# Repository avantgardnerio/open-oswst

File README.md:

# open-oswst

Stealth LoRa radio mesh where the primary design principle is "only speak when spoken to": a simplex push-to-talk voice radio over
LoRa, with flood repeaters, that transmits nothing until someone presses PTT.

## Hardware

- **Board**: [Heltec WiFi LoRa 32 V4.3](https://heltec.org/project/wifi-lora-32-v4/) (ESP32-S3 + SX1262, 863-928 MHz)
- **MCU**: ESP32-S3 rev 0.2, 16MB flash, ~380 KiB RAM, no PSRAM
- **Radio**: Semtech SX1262 LoRa transceiver, 915 MHz ISM band, behind the board's KCT8103L front-end module (PA + LNA), then an
  external "Air Buddy" amplifier. The SX1262 runs at 6 dBm, which should give roughly 1 W out of the Air Buddy (estimated from datasheets,
  not measured)
- **GPS**: L76K on the Heltec's GNSS connector (UTC time and position, logged and shown on screen)
- **Display**: SSD1306 128x64 OLED (I2C)
- **Audio**: MAX9814 electret mic (ADC), MAX98357A I2S class-D speaker amp

The board is a V4.3. All the boards we've tested are; a V4.2 (GC1109 front end) would need different FEM pins and TX power.

### Pin Map

`src/board.rs` is the one place pins are assigned; this table mirrors it.

| Function | GPIO | Notes |
|---|---|---|
| PTT (PRG button) | 0 | Active LOW, internal pull-up |
| VOL encoder A / B / SW | 3 / 6 / 45 | GPIO45 is a strapping pin, safe as a switch to GND |
| Mic (ADC1) | 4 | MAX9814 out |
| Speaker I2S BCLK / DIN / WS | 47 / 33 / 48 | MAX98357A |
| OLED SDA / SCL / RST | 17 / 18 / 21 | |
| Vext power enable | 36 | LOW = on (OLED) |
| LoRa SCK / MOSI / MISO / NSS | 9 / 10 / 11 / 8 | SPI2 |
| LoRa RST / DIO1 / BUSY | 12 / 14 / 13 | |
| FEM power / enable (CSD) | 7 / 2 | Held HIGH while running |
| FEM CTX | 5 | HIGH only during TX (LOW = RX through the LNA) |
| GPS UART RX / TX | 39 / 38 | ESP side. Meshtastic's variant file comments have these the other way round |
| GPS power / reset / wake | 34 / 42 / 40 | Power is active LOW |
| Battery sense | 1 (+ 37 enables the divider) | Free for this on the newest PCB rev; not used by the firmware yet |

## Dev Environment Setup

### Prerequisites

1. **Install Rust + Xtensa toolchain** via [espup](https://github.com/esp-rs/espup):

```bash
cargo install espup
espup install
```

2. **Create an ESP environment export script** (`~/export-esp.sh`):

```bash
export LIBCLANG_PATH="$HOME/.rustup/toolchains/esp/xtensa-esp32-elf-clang/esp-20.1.1_20250829/esp-clang/lib"
export PATH="$HOME/.rustup/toolchains/esp/xtensa-esp-elf/esp-15.2.0_20250920/xtensa-esp-elf/bin:$PATH"
```

The exact paths may vary — check `~/.rustup/toolchains/esp/` after `espup install`.

3. **Install flashing tools**:

```bash
cargo install espflash cargo-espflash ldproxy
```

4. **Python tools** (log pulling, PCB and case generation) live in a venv built with Python 3.13:

```bash
python3.13 -m venv .venv
.venv/bin/pip install -r requirements.txt
```

### Build

```bash
. ~/export-esp.sh
cargo build                      # firmware (repo root, ESP32-S3)
(cd core && cargo test)          # app logic unit tests, on this PC
(cd desktop && cargo run)        # desktop build (a skeleton so far)
```

ESP-IDF v5.5.x is downloaded automatically by `esp-idf-sys` on first build (takes a while).

### Flash

Over USB, use the script. It flashes every connected board at once, and passes the three things a bare `espflash flash` gets wrong:

```bash
. ~/export-esp.sh && cargo build && scripts/flash-all.sh
```

- **our bootloader** (`--bootloader`): it switches the flash to QIO. espflash's bundled one is DIO
- **our partition table** (`--partition-table`): espflash's default drops the `storage` partition and the OTA slots
- **`--erase-parts otadata`**: otherwise a board last updated over WiFi keeps booting the other slot

Over WiFi, see [In the Field](#in-the-field).

Serial ports aren't stable between plug-ins: identify boards by MAC (the ESP32-S3's USB serial number), not by `ttyACM` number. To capture a
boot log from the first line, `python3 scripts/boot-log.py <PORT>`. Never flash while another program holds the port.

### Device Config

Each board's settings are a text file on its storage: `/data/config.toml`. On the newest PCB rev the on-device menu (click the VOL knob)
sets the mode and rewrites the file. Every setting and flag is declared in `core/src/config.rs`; each boot logs their values
and a 4-digit settings profile (also in `/api/status`): radios with different profiles can't hear each other.

```toml
mode = "repeater"        # normal | repeater | echo

[flags]                  # experiments, come and go (core/src/config.rs lists them)

[[wifi]]                 # networks to join, tried in order
ssid = "Starlink"
password = "..."
```

`scripts/provision.py` writes it over USB, from `boards.toml` in the repo root (kept out of git: it holds WiFi passwords; copy
`boards.example.toml` to start). It flashes the firmware too, and **erases the board's storage**, logs included: pull them first.

```bash
.venv/bin/python scripts/provision.py                      # every connected board
.venv/bin/python scripts/provision.py A4:CB:8F:A2:0F:5C    # just this one
```

The boot log shows the result, e.g. `Config: mode=Echo, 1 WiFi network(s)`.

### Logs

Every boot writes a text log to `/data/sd/log/NNNN.txt` on the board's SD card (LittleFS, `src/devices/sd.rs`). Lines are buffered in
RAM and written by a low-priority thread once a second: unlike the chip's own flash, the card stalls nothing, so repeaters log too. No
card, no log. Copy them off over WiFi (WebDAV, below: `/fs/sd/log/`). `scripts/pull-logs.py` reads the flash over USB, so it only
finds logs from before the card.

After an echo test, join the handheld's and the echo station's logs into a per-transmission table and a map (OpenStreetMap/satellite,
one circle per transmission coloured by how well each direction got through, plus GeoJSON for QGIS):

```bash
.venv/bin/python scripts/range-report.py <handheld log> <echo station log>
```

## In the Field

Every radio has the field hotspot (Starlink) in its `config.toml` and stays on WiFi, so in the field the laptop does everything over
WiFi: find the radios, read their status and logs, change their config, update their firmware. USB is the fallback.

### Laptop setup (once, at home)

```bash
sudo apt install avahi-utils curl    # avahi-browse finds the radios; Ubuntu resolves *.local out of the box
```

Plus the build tools above (`espup`, `espflash`, `~/export-esp.sh`), so firmware can be built and saved as an image in the field.

### Find the radios

Join the laptop to the same network as the radios, then:

```bash
avahi-browse -rtp _oswst._tcp | grep "^="    # one line per radio: name, host, IP, port
```

Each radio is `oswst-XXXX.local`, from the last 4 hex digits of its MAC (A4:CB:8F:A2:0F:5C is `oswst-0f5c`). A radio joins WiFi ~7 s
after boot. If a radio doesn't show up:

- `getent hosts oswst-0f5c.local`: asks for one radio by name
- check that avahi-browse ran at all. Don't pipe its errors into grep: if it isn't installed, `2>&1 | grep` prints nothing,
  which looks exactly like "no radios"
- last resort, scan the subnet for the API:
  `for i in $(seq 1 254); do curl -s -m 1 http://192.168.0.$i/api/status | grep -q mac && echo 192.168.0.$i & done; wait`

### Talk to a radio

In a browser: `http://oswst-XXXX.local/` (or its IP) opens the radio's web page, its status and a live picture of its screen
(`www/`, served by the radio itself: no internet needed).

Port 80, no password (the WiFi password is the security). `/fs/` is the radio's storage as a read-write WebDAV folder
(`src/webdav.rs`): open `dav://oswst-XXXX.local/fs/` in a file manager, or:

```bash
R=oswst-0f5c.local
curl http://$R/api/status                     # name, MAC, firmware (git hash, confirmed?), OTA slot, mode, uptime, heap
gio list -l dav://$R/fs/sd/log/               # after `gio mount dav://$R/fs/`
curl -O http://$R/fs/sd/log/0007.txt          # fetch a log: 25 KB in under 0.1 s (vs ~80 s over USB)
curl -O http://$R/fs/config.toml              # the settings
curl -T config.toml http://$R/fs/config.toml  # replace them (checked first: a bad file is refused); apply on reboot
curl -X POST http://$R/api/reboot
curl -X POST http://$R/api/wifi/off           # WiFi off until the next power cycle (for timing-sensitive tests)
```

`/api/wifi/off` isn't saved: every boot starts with WiFi on again, so a power cycle always gets the radio back on the network. Once it's
off, the radio can't be reached over WiFi until then.

### Update firmware over WiFi (OTA)

Build, save an app image, put it on the radio as `/fs/sd/firmware.bin` (an ordinary file: a file manager works too), then
`POST /api/ota`: the radio copies it into its spare slot and reboots into it (back up in ~15 s). `/api/status` then shows the new
git hash, the other slot and `"firmware_state":"pending"`: a new app must run a minute (then `valid`), or the radio goes back to the
old one. `GET /api/firmware` downloads the app a radio is running.

```bash
. ~/export-esp.sh && cargo build
espflash save-image --chip esp32s3 target/xtensa-esp32s3-espidf/debug/open-oswst app.bin
curl -T app.bin http://oswst-0f5c.local/fs/sd/firmware.bin && curl -X POST http://oswst-0f5c.local/api/ota
```

Every radio found:

```bash
for host in $(avahi-browse -rtp _oswst._tcp | grep "^=" | cut -d';' -f7 | sort -u); do
    curl -T app.bin http://$host/fs/sd/firmware.bin && curl -X POST http://$host/api/ota
done
```

### USB fallback

When a radio isn't on WiFi:

- **Flash:** `scripts/flash-all.sh`. It passes our bootloader, our partition table and `--erase-parts otadata`, which a bare
  `espflash flash` gets wrong.
- **Pull logs:** `scripts/pull-logs.py` (~80 s).
- **Watch a boot:** `scripts/boot-log.py`.

Identify boards by MAC, not by `ttyACM` number, and never flash while another program holds the port.

## Management Server

Radios get updates from a management server (`server/`, issue #34) that they dial out to: nothing on a radio listens for it. Every
connection is Noise: a radio must know the server's public key, and the server must find the radio's in its list, or it's refused.
The server's files live in one folder outside the repo (default `/srv/oswst`):

```
server.key      the server's key pair (mode 0600)
radios.toml     the radios allowed in: re-read at every connection, no restart needed
bundle.tar.gz   THE update: radios that don't have it are offered it
```

```bash
cd server && cargo run --release -- keygen /srv/oswst     # once: prints the server's public key
cd server && cargo run --release -- /srv/oswst            # run it by hand (port 3101)
```

To keep it running, install it as the systemd service `oswst-server` (`server/oswst-server.service`). It runs as its own user,
`oswst`, which can only read `/srv/oswst`. Run the same script again after you change `server/`:

```bash
scripts/install-server.sh                                 # build, install, (re)start
sudo journalctl -u oswst-server -f                        # its log
```

### Publish an update

```bash
scripts/publish-firmware.sh          # builds, then writes /srv/oswst/bundle.tar.gz
```

A bundle (`core/src/bundle.rs`) is one `.tar.gz`: `firmware.bin` for the radio's spare app slot, and `www/` (the web page, with
only the `node_modules` files its import map names) for its storage. The server notices the new file by itself.

### Install it

On the radio: **menu, Update**. It shows the version and size, then **Install** runs three steps, each in percent: **Downloading**
(to the storage), **Verifying** (its SHA-256), **Extracting** (the firmware into the spare slot, marked to boot only once every
file is written; the files onto the storage, never touching `config.toml` or `secrets.toml`). Then it reboots into the new
firmware, which must run a minute to be kept. A radio that has the bundle is told **Up to date**.

`POST /api/management/update` does the same from a laptop. Radios on firmware from before bundles are offered just the firmware
inside the bundle; one more Update then gets the whole bundle.

### Set up a new radio

1. **Provision over USB** (once). Give the radio an entry in `boards.toml` (its mode, name, WiFi networks), then:

   ```bash
   . ~/export-esp.sh && cargo build
   .venv/bin/python scripts/provision.py 10:BD:A3:5A:EB:7C
   ```

   This flashes the firmware and writes a fresh storage holding just its `config.toml` (it **erases** the storage). The radio
   boots, joins WiFi, and makes its own key pair: the private key never leaves it.
2. **Enroll it on the server.** Its public key is on its status page; add it to `/srv/oswst/radios.toml`:

   ```bash
   curl -s http://oswst-eb7c.local/api/status    # "management": {"radio_public_key": "..."}
   ```

   ```toml
   [[radio]]
   name = "Repeater"
   mac = "10:BD:A3:5A:EB:7C"
   public_key = "38389dbc..."
   ```
3. **Tell it where the server is** (and the server's public key, from `keygen`):

   ```bash
   curl -X PUT -H "Content-Type: application/json" \
        -d '{"host": "<server host>", "port": 3101, "server_public_key": "<64 hex digits>"}' \
        http://oswst-eb7c.local/api/management
   ```
4. **Menu, Update.** A radio flashed over USB doesn't have the bundle yet, so it's offered it: that brings the web page too.

A re-provisioned radio has a new key (the storage was erased), so it's enrolled again: replace its `public_key` in `radios.toml`.
To shut a lost radio out, delete its entry.

## Current Behavior

- **Voice**: simplex push-to-talk. Hold PTT to talk: audio is Codec2-encoded at 1200 bps and streamed as 4-frame LoRa packets (160 ms of
  audio each, SF7/125 kHz). Release to listen: received packets are decoded in order and played through the speaker. A lost packet
  costs one 160 ms gap of silence, and a corrupt one is dropped rather than resetting playback. PTT does nothing while someone else's
  transmission is on the air: no talking over each other
- **Modes**: normal; **repeater** (relays the first copy of each packet once, one hop further: flood style, but a copy that loops back
  is a duplicate); **echo** (records a transmission, then plays it back over the air, for range testing alone). Set in
  `/data/config.toml`
- **Screen**: short MAC and UTC time, GPS position, RX/TX state, RSSI and SNR of received audio, and volume
- **Controls**: VOL knob turns volume; clicking it opens the menu (Lock, Mode). Needs the newest PCB rev's wiring (see Pin Map)
- **Logs**: persistent per-boot text logs including a GPS fix every 30 s, so field tests can be mapped afterwards
- **Timing**: the air is a conveyor of 80 ms bins (`core/src/conveyor.rs`). A talker sends packet n in bin 2n and each repeater relays
  it one bin later, so hop h of packet n is in bin 2n + h; the header's hop count says which. Every packet starts at its microsecond, in
  the middle of its bin (the radio sends it then). A receiver counts bins from the first good packet it hears, so every copy of a packet
  is the same packet, and a garbled packet in a bin still keeps the transmission going. Only a talker's first packet waits for clear air
- **Listening**: during a transmission the radio turns through a schedule of channels, bin by bin (`core/src/climb.rs`): it holds the
  channel with the strongest copies in their bins, and in the others always seeks one channel on and one back. A side that's clearly
  stronger becomes the hold, so a listener climbs to the best copy of several repeaters'. Only the first copy of each packet plays
- **Next up**: frequency hopping and encryption

<!-- air-diagram: generated by scripts/air-diagram.py; edit the script, not this section -->
## On the Air (SF7 / 125 kHz)

LoRa SF7, 125 kHz, coding rate 4/5, explicit header, 12-symbol preamble (`core/src/air.rs`). One symbol is 2^7 / 125 kHz =
**1.024 ms**. Air times are Semtech's formula on our constants; regenerate this section with `python3 scripts/air-diagram.py`
after changing one.

### Voice packet: 26 bytes, 64.25 symbols, 65.8 ms

```
symbol 0           12     16.25   24.25                                   64.25
       +-----------+------+-------+----+----+----+----+----+----+----+----+
       |  preamble | sync |  PHY  | B1 | B2 | B3 | B4 | B5 | B6 | B7 | B8 |
       |   12 sym  | 4.25 | header|            8 blocks x 5 sym           |
       |           | sym  | 8 sym |        28 bits each = 224 bits        |
       |           |      |       |        = 26 B payload + 2 B CRC       |
       +-----------+------+-------+----+----+----+----+----+----+----+----+
ms     0           12.3   16.6    24.8                                    65.8
```

- **sync**: 2 sync-word symbols + 2.25 start-of-frame symbols
- **CRC**: ours (`core/src/crc.rs`, CRC-16/CCITT-FALSE), appended and checked by the radio driver, with LoRa's own CRC off: the
  same 16 bits on the air. LoRa only checks its CRC if the received header says there is one, and noise can corrupt a header
  into "no CRC" and still pass its checksum; ours is checked on every packet, so garbage never reaches the app
- **PHY header**: 20 bits (payload length, coding rate, CRC flag (off), header checksum), always sent at CR 4/8: 8 symbols (at
  SF7, nothing else fits)
- **blocks**: each 5-symbol block carries 28 data bits. 26 bytes + CRC fill 8 blocks exactly; one more byte costs another block
  (+5 symbols, +5.1 ms)

The 26 bytes:

```
byte   0               2           8           14          20          26
       +---------------+-----------+-----------+-----------+-----------+
       |   our header  |   Codec2  |   Codec2  |   Codec2  |   Codec2  |
       |   (2 bytes)   |  frame 1  |  frame 2  |  frame 3  |  frame 4  |
       |               |  6 bytes  |  6 bytes  |  6 bytes  |  6 bytes  |
       |               |  = 40 ms  |  = 40 ms  |  = 40 ms  |  = 40 ms  |
       +---------------+-----------+-----------+-----------+-----------+

our header, 16 bits, big-endian (core/src/packet.rs):
bit     15     11 10          4 3       1 0        0
       +---------+-------------+---------+----------+
       | type 5b |   txid 7b   | hops 3b | spare 1b |
       +---------+-------------+---------+----------+
       type: 0 voice, 1 echo replay, 2 wake, 3 voice end, 4 echo end (core/src/packet.rs PacketType)
       txid: random per transmission; hops: repeaters this copy came through, 0 from the talker; spare: 0
```

### Wake packet: 2 bytes, 64.25 symbols, 65.8 ms

Sent once, first, so radios sweeping the hop channels can find the transmission. The preamble takes up the air the audio would
have used, so it fits a slot like any packet: 12 + (48 − 18) = 42 symbols.

```
symbol 0                                         42     46.25   54.25     64.25
       +-----------------------------------------+------+-------+----+----+
       |                 preamble                | sync |  PHY  | B1 | B2 |
       |      42 sym: a sweeping radio's CAD     | 4.25 | header| 2 B hdr |
       |      (2 sym) can land in the first      | sym  | 8 sym |  + CRC  |
       |            40 symbols (41 ms)           |      |       |         |
       +-----------------------------------------+------+-------+----+----+
ms     0                                         43.0   47.4    55.6      65.8
```

### End packet (EOT): 26 bytes, 64.25 symbols, 65.8 ms

The last packet of every transmission says who sent it and where they were: a voice packet's size and air, so it fits a
repeater's slot like one. The talker sends its own; a repeater relays it unchanged; an echo station ends its replay with its
own. The screen shows who was last heard, how far away, and through a repeater or not.

```
byte   0               2           5           8                                26
       +---------------+-----------+-----------+--------------------------------+
       |  our header   | latitude  | longitude |  name, UTF-8, up to 18 bytes   |
       | type 3 or 4   | 24 bits   | 24 bits   |          zero-padded           |
       +---------------+-----------+-----------+--------------------------------+
       latitude: ±90° in ±2^23 steps (~1.2 m); longitude: ±180° (~2.4 m); -2^23 latitude = no fix
```

### A transmission

```
PTT pressed
 +160 ms   wake packet         64.25 sym   (sent while the first 160 ms of audio is captured)
 ~320 ms   voice packet 0      64.25 sym   then one voice packet every 160 ms (156.25 sym)
     ...
 release   last voice packet, then EOT    64.25 sym  (who and where)
```

An echo station sends its wake packet one slot before its replay. A repeater relays a wake packet like any other (once per
transmission), so radios that only hear the repeater can find it.

### One slot with a repeater: 160 ms = 156.25 symbols

Talkers don't hop yet (`tx_hops = 0`): every transmission stays on the start slot, channel 0. Receivers sweep `rx_hops`
channels, and with the sweep flag a repeater relays each packet on the next of those after the one it heard it on (channel 1
here), then goes back to listening on channel 0. It relays as soon as it has the packet, inside the gap before the talker's next
one. Repeater steps are medians of 226 relays (the talker's packets and the echo station's replays) measured on the desk
(`out/relay-test/20261005-150052`).

```
symbol    0                               64.25                                137      156.25
          |                               |                                    |        |
talker    [=== voice packet n ============]                                             [== packet n+1
repeater   . RX (locked) .................]ttt[===== relay of packet n ========]b. RX ..[
                                           ^ t: RX done -> relay on air 7.8 ms
                                                                                ^ b: back to RX 1.5 ms
                                                                                <-- slack 17.9 ms -->
ms        0                               65.8                                 140.6    160
```

| Step (repeater) | Median | Symbols | |
|---|---|---|---|
| RX done → relay starts | 5.4 ms | 5.2 | `t`: read the packet out, the app hands it back to the radio |
| standby | 0.9 ms | 0.8 | `t` |
| prep (packet, modulation, buffer) | 1.5 ms | 1.5 | `t` |
| tx: TX command → TxDone | 67.1 ms | 65.5 | 65.8 ms on the air + PA ramp and IRQ |
| back to RX | 1.5 ms | 1.5 | `b` |
| **slack before packet n+1** | **17.9 ms** | **17.5** | a relay ending later than this deafens the repeater to the next packet |

Each repeater uses ~142 of the 160 ms. A second repeater in the chain can't fit the same slot on the same channel; that's what
hopping (each repeater relays on the next channel) is for.
<!-- /air-diagram -->

## Key Implementation Notes

- **Framework**: esp-idf-svc 0.52.1 (std Rust, not bare-metal)
- **Async**: `block_on` + `embassy_futures::select`; the app sleeps until an event (packet, PTT, speaker, knob) or a 250 ms housekeeping tick
- **LoRa driver**: `lora-phy` (lora-rs git main) with `GenericSx126xInterfaceVariant`; DIO2 drives the FEM's TX/RX path, GPIO5 its RX LNA
- **Hardware-free app**: everything above the drivers is in `core/` behind small device traits, so it runs and is tested on a PC
- **Storage**: LittleFS (`joltwallet/littlefs` component), chosen over FAT for power-cut safety: the flash partition at `/data` holds
  the settings (`config.toml`, `secrets.toml`); the SD card at `/data/sd` everything else (logs, web app, updates)
- **SPI async**: `CONFIG_SPI_MASTER_ISR_IN_IRAM` disabled in `sdkconfig.defaults`
- **defmt workaround**: `defmt-discard.x` linker script discards defmt sections that break ESP-IDF flash layout
- **Stack**: 65536 bytes for main task (Codec2 init needs large stack temporaries)

## Project Structure

Four Cargo workspaces. Each opens as its own IDE project: the firmware builds for the ESP32-S3, the others for this PC.

```
src/                 # Firmware (repo root workspace, xtensa)
  main.rs            #   Brings up the board and runs the core app on it
  board.rs           #   The one place pins are assigned
  devices/           #   ESP drivers: radio, fem, gps, mic, speaker, screen, encoder, ptt, settings, storage
  bin/               #   Bringup tests (fem_probe, gps_test, storage_test, batt_probe, loopbacks, ...)
core/                # Hardware-free app: its own workspace, so `cargo test` runs on this PC
  src/app.rs         #   Event loop, screens, housekeeping
  src/conveyor.rs    #   A transmission's bins: which packet each copy is, when it's over (unit tested)
  src/climb.rs       #   Which channel to listen on, bin by bin: hold the strongest copy, seek beside it (unit tested)
  src/playout.rs     #   Decoded packets to the speaker in order, silence for lost ones (unit tested)
  src/codec.rs       #   Codec2 thread
  src/management.rs  #   The management server's protocol (Noise), shared with server/
  src/bundle.rs, tar.rs, gzip.rs   # Update bundles: what goes where, streamed off a .tar.gz (unit tested)
  src/echo.rs, mode.rs, menu.rs, packet.rs, logger.rs
  src/devices/       #   Device interfaces: radio/speaker/screen channels, gps/mic/ptt/knob/settings traits
desktop/             # Desktop build on virtual devices (skeleton so far)
server/              # The management server: radios' keys, update bundles
www/                 # The radio's web page (preact + htm, no build step), shipped in bundles
scripts/             # provision.py, publish-firmware.sh, boot-log.py, pull-logs.py, ...
pcb/                 # PCB definition (Python DSL) and generated KiCad board
models/              # Parametric case (build123d) and fit check
partitions.csv       # Partition table: two OTA app slots, LittleFS storage (/data)
boards.example.toml  # Per-board settings for scripts/provision.py (copy to boards.toml)
sdkconfig.defaults   # ESP-IDF config overrides
```

## Bill of Materials

### Handset (~$122)

| Component                                                                                       | Part                                                       | Qty | Est. Cost |
|-------------------------------------------------------------------------------------------------|------------------------------------------------------------|-----|-----------|
| [MCU + LoRa + GPS](https://www.amazon.com/dp/B0GCD9W6JZ?ref=ppx_yo2ov_dt_b_fed_asin_title&th=1) | Heltec WiFi LoRa 32 V4                                     | 1   | $42       |
| [RF amplifier](https://www.amazon.com/dp/B0DQBJVR91?ref=ppx_yo2ov_dt_b_fed_asin_title)          | AB-IOT-868 "Air Buddy" (902-928 MHz, bidirectional TX+LNA) | 1   | $26       |
| [Speaker amp](https://www.amazon.com/dp/B0DPJRLMDJ?ref=ppx_yo2ov_dt_b_fed_asin_title)           | MAX98357A I2S Class D breakout                             | 1   | $3        |
| [Speaker](https://www.amazon.com/dp/B0BTP67F81?ref=ppx_yo2ov_dt_b_fed_asin_title&th=1)          | 8 ohm 1W mini (JST-PH1.25mm)                               | 1   | $2.50     |
| [Microphone](https://www.amazon.com/dp/B0B7SP6GYX?ref=ppx_yo2ov_dt_b_fed_asin_title)            | MAX9814 electret with AGC (analog out)                     | 1   | $4        |
| [Antenna](https://www.amazon.com/dp/B0D47HVCK7?ref=ppx_yo2ov_dt_b_fed_asin_title&th=1)          | 5 dBi SMA whip (915 MHz)                                   | 1   | $6        |
| [Battery](https://www.amazon.com/dp/B0FPCWFFYB?ref=ppx_yo2ov_dt_b_fed_asin_title)               | YELUFT 1S 103450 3.7V 2000mAh LiPo (JST 1.25)              | 1   | $24       |
| [encoder](https://www.amazon.com/dp/B07F24TRYG?ref=ppx_yo2ov_dt_b_fed_asin_title)               | EC11 rotary encoder w/ push button (Taiss)                 | 2   | $1.25     |
| [Power switch](https://www.amazon.com/dp/B0DN69L9SG?ref=ppx_yo2ov_dt_b_fed_asin_title&th=1)     | SS12F15 mini slide switch (SPDT)                           | 1   | $0.30     |
| [PTT button](https://www.amazon.com/dp/B015X34IP6?ref=ppx_yo2ov_dt_b_fed_asin_title&th=1)       | Ulincos U16A1 16mm metal momentary, flush                  | 1   | $8        |
| [Speaker jack](https://www.amazon.com/dp/B01ASF0LW8?ref=ppx_yo2ov_dt_b_fed_asin_title)          | 2.5mm TRS chassis mount (Calrad 30-714 or similar)         | 1   | $0.66     |
| [Mic/PTT jack](https://www.amazon.com/dp/B00ZYWJ1DG?ref=ppx_yo2ov_dt_b_fed_asin_title)          | 3.5mm TRS chassis mount w/ switch (CESS)                   | 1   | $2        |
| [F2F SMA](https://www.amazon.com/dp/B0FB3R5WRL?ref=ppx_yo2ov_dt_b_fed_asin_title&th=1)          | Female to Female SMA                                       | 1 | $1        |

## Related Projects

Voice over LoRa is rare. This is what we found as of October 2026, with our own status stated the same way as everyone else's.

| Project | What it does | Repeating | Licence | Status |
|---|---|---|---|---|
| **open-oswst** (this) | Live push-to-talk, Codec2 1200 bps, handheld with case and PCB | Flood repeater mode exists, but more than one repeater degrades audio; making multi-repeater flooding work is the current focus | None (US 902–928 MHz ISM) | Live voice works handheld to handheld; field-tested to ~600 m through suburbs (GPS-logged). No encryption or frequency hopping yet |
| [QMesh](https://github.com/faydr/QMesh) ([project](https://hackaday.io/project/161491-qmesh-a-lora-based-voice-mesh-network), [paper](https://cdn.hackaday.io/files/1614916909230944/TAPR%20DCC%202020%20Paper.pdf)) | Live voice, Codec2, 160 ms frames | **Synchronised flooding:** every node retransmits at once in TDMA slots, with extra FEC and deliberate timing/frequency offsets so the copies don't destructively collide, plus per-packet hopping. Reported 99% packet reception with 2–3 simultaneous retransmitters | Amateur (US Technician) | **Ahead of us on radio techniques.** STM32 dev boards + custom shield. No commits since December 2022 |
| [Mesh-Talkie](https://github.com/WIH4/Mesh-Talkie) | Planned PTT handheld, ESP32-S3 + SX1262 (our hardware), AES-256 | Planned flood mesh with TTL | None (EU SRD) | Design documents only: no hardware or firmware yet |
| [esp32_loradv](https://github.com/sh123/esp32_loradv) | Codec2/Opus digital-voice walkie-talkie | None (point to point) | Amateur (70 cm) | Hobby project |
| Meshtastic, [MeshCore](https://github.com/RipeStore/meshcorebuilder), [MeshTRX](https://github.com/StanislavButkovsky/meshtrx) | Text mesh messengers | Yes, for text | None | Mature for text; voice is recorded clips forwarded later, not live PTT |
| [dudmuck/lora_codec2](https://github.com/dudmuck/lora_codec2), [Lora-Voice-Image-Text](https://github.com/chicodog530/Lora-Voice-Image-Text), [ESP32_Codec2](https://github.com/deulis/ESP32_Codec2) | Codec2-over-LoRa demos | None | — | Demos |

As far as we can tell, nobody else has live push-to-talk voice over LoRa working on handhelds **without a licence**. The hard part, several repeaters sharing one channel, is unsolved here; QMesh has gone furthest on it, and under an amateur licence.

## License

TBD

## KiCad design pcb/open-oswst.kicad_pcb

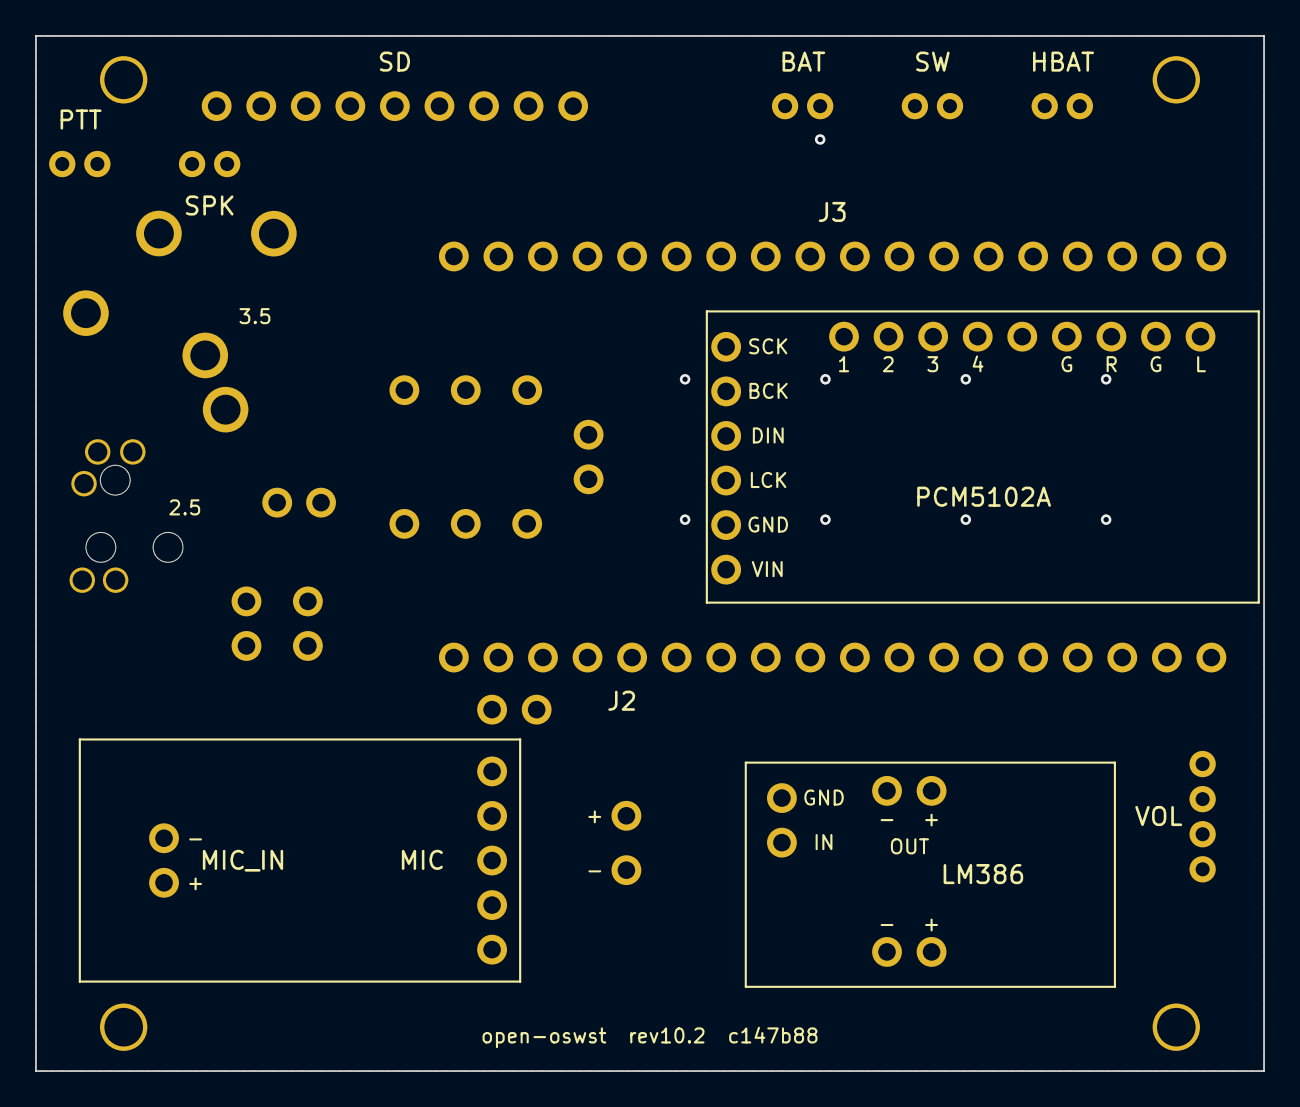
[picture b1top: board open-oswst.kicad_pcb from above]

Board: 2 copper layers, 70.0 x 59.0 mm, 28 parts (0 on the bottom side), 22 nets, no tracks yet.

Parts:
BAT: JST_PH_B2B
C1: PinHeader_1x2_P2.5mm
C2, C3, C4: PinHeader_1x2_P2.54mm
CAPSULE: PinHeader_1x2_P3.1mm
H1, H2, H3, H4: MountingHole_2.2mm
HBAT: JST_PH_B2B
J2, J3: PinHeader_1x18_P2.54mm
JP1: PinHeader_1x2_P2.54mm
K1_2.5: K1_Jack_2.5mm_measured
K1_3.5: K1_Jack_3.5mm_measured
LM386: LM386_mini
MIC: PinHeader_1x5_P2.54mm
MIC_IN: PinHeader_1x2_P2.54mm
PCM: PCM5102A_GY
PTT: JST_PH_B2B
R1, R2, R3: PinHeader_1x2_P7.62mm
SD: PinHeader_1x9_P2.54mm
SPK: JST_PH_B2B
SW: JST_PH_B2B
VOL: JST_PH_B4B

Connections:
ADC: C2.1, J3.GPIO4, R3.2
AMP_IN: LM386.2, PCM.7
AMP_OUT: K1_2.5.2, LM386.4
BCLK: J2.GPIO47, PCM.5
BIAS: C1.+, R1.2, R2.1
CAPSULE: CAPSULE.+, K1_3.5.4
DIN: J2.GPIO33, PCM.4
GND: BAT.-, HBAT.-, J2.GND, J3.GND, JP1.GND, LM386.1, LM386.3, LM386.5, PCM.2, PCM.6, PCM.12, PCM.14, PCM.15, PTT.2, SD.GND, SPK.-, VOL.GND
KNOB_SCL: J3.GPIO6, VOL.SCL
KNOB_SDA: J3.GPIO3, VOL.SDA
LRC: J2.GPIO48, PCM.3
MIC_GND: C1.-, C2.2, C3.2, C4.2, CAPSULE.-, JP1.MIC_GND, K1_2.5.3, MIC.GND, MIC_IN.-
MIC_IN: C3.1, C4.1, K1_3.5.5, MIC_IN.+, R2.2
MIC_OUT: MIC.OUT, R3.1
PTT: J2.GPIO0, K1_3.5.3, PTT.1
SD_CLK: J3.GPIO45, SD.CLK
SD_CMD: J2.GPIO43, SD.CMD
SD_D0: J2.GPIO44, SD.DO
SPK+: K1_2.5.1, SPK.+
VBAT: BAT.+, SW.1
VSW: HBAT.+, SW.2
Ve: J2.Ve_a, J2.Ve_b, LM386.6, MIC.GAIN, MIC.VDD, PCM.1, PCM.13, R1.1, SD.3V3, SD.D3, VOL.3V3

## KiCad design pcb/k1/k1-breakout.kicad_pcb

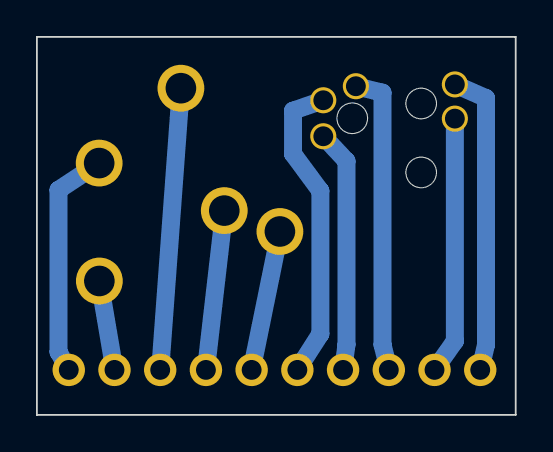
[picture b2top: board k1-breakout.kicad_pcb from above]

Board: 2 copper layers, 26.6 x 21.0 mm, 3 parts (0 on the bottom side), 10 nets.

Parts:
H: PinHeader_1x10_P2.54mm_milled
J2.5: K1_Jack_2.5mm_measured
J3.5: K1_Jack_3.5mm_measured

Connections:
J25_1: H.7, J2.5.1
J25_2: H.6, J2.5.2
J25_3: H.8, J2.5.3
J25_4: H.9, J2.5.4
J25_5: H.10, J2.5.5
J35_1: H.2, J3.5.1
J35_2: H.1, J3.5.2
J35_3: H.3, J3.5.3
J35_4: H.4, J3.5.4
J35_5: H.5, J3.5.5

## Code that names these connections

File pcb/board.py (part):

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board.add_jst_ph(cx, cy, pins=2, label="SW",
                 pad_nets=["VBAT", "VSW"]); cx += JST2_STEP
board.add_jst_ph(cx, cy, pins=2, label="HBAT",
                 pad_labels=["+", "-"], pad_nets=["VSW", "GND"]); cx += JST2_STEP

# PTT (rev 10.1): top-left corner, under the screw, beside the K1 jack whose
# sleeve is wired to it. At the top right, the PTT net ran the whole top
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# button is in the right wall, so its cable is long now (~60 mm)
PTT_X = BX + 2.5
PTT_Y = BY + 7.3
board.add_jst_ph(PTT_X, PTT_Y, pins=2, label="PTT",
                 pad_nets=["PTT", "GND"])
# The internal speaker (rev 10.2), beside PTT: it hangs off the K1 2.5 jack's
# tip switch below. Up on the top edge beside SD the SD bus and the PCM's
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MIC_Y = BY + 47
CAPSULE_DIAMETER = 9.74  # micrometer, 2026-11-06
CAPSULE_X = (MIC_X + 0.85 + LM386_LEFT) / 2
# CAPSULE turned 270 degrees: pin 1 north (frame (0, -y) = y mm east,
# (x, 0) = x mm south); MIC_IN 90, like the amp's header: pin 1 south
# (frame (0, y) = y mm east). Names clear of pads and outlines
# GAIN to VDD = 40 dB: 60 dB (floating) swung rail to rail on the bench, 50
# clipped the Disco32. GND is the mic ground (JP1 joins it to the board's)
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# Turned with the amp board's header (user, 2026-11-06): "+" south. Which
# Q1 pad is the input gets checked at assembly: it idles at the amp's
# MICBIAS (~2 V through 2.2k), the other is its ground
board.add_header(MIC_X - MIC_Q1, MIC_Y, pins=2, label="MIC_IN", angle=90,
                 pad_labels=["+", "-"], pad_nets=["MIC_IN", "MIC_GND"], ref_at=(0, 4.5))
# The board's own mic: the 9x7 mm electret capsule, on the K1 3.5 jack's
# ring NC switch (net CAPSULE, K1_NETS): plugging a headset in opens the
# switch and the headset's mic, on the ring, takes over. Between the two amp
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CAPSULE_Y = MIC_Y - 1.0
CAPSULE_PITCH = 3.1  # its legs, off a marked-up photo (3.1-3.2 mm, 2026-11-06)
board.add_circle(CAPSULE_X, CAPSULE_Y, CAPSULE_DIAMETER, layer="B.SilkS", width=0.12)
board.add_header(CAPSULE_X, CAPSULE_Y, pins=2, label="CAPSULE", angle=270, pitch=CAPSULE_PITCH,
                 pad_labels=["+", "-"], pad_nets=["CAPSULE", "MIC_GND"], ref_at=(6.5, 0),
                 ref_layer="B.SilkS")  # its name on its own side, clear of both outlines
# Which hole is which, on both sides (the capsule faces the floor, the amp
# board's leads come from the lid side): "+" (pin 1) north
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

# The jack pins the mic half uses (rev 11), by (jack, pin) from the bench map
# (rev 10 header pin -> function, 2026-10-27/11-05): 3.5 sleeve = PTT to
# ground, 3.5 ring = the headset mic, 3.5 ring's NC switch = the board's
# capsule (open with a plug in), 2.5 sleeve = the headset mic's ground.
# Rev 10.2, the speaker half: 2.5 tip = the LM386's output (the headset's
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# Its name and value as one label, below it: above it is the Heltec's edge
# Fitted from the back with the passives, so labelled there
board.add_header(MIC_X + 1.27, BY + 38.4, pins=2, label="JP1",
                 pad_labels=["MIC_GND", "GND"], pad_nets=["MIC_GND", "GND"], ref_hidden=True)
board.add_text(MIC_X + 1.27, BY + 40.0, "JP1 0R", layer=BACK_SILK, size=0.8, thickness=0.12)

# Silkscreen — project name, revision and git SHA
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
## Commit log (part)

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2026-04-24 docs
2026-04-25 scripts
2026-04-25 logging
2026-04-25 [WIP] move codec to it's own thread
2026-04-25 [WIP] style
2026-04-25 [WIP] timing plot
2026-04-27 [WIP] speaker refactor more
